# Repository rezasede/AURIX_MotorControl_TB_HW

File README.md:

# GaN FET PMSM Motor Control Test Bench — PCB Hardware

A two-board, 3-phase **GaN-based inverter** for driving a **PMSM / BLDC motor** with Field-Oriented Control (FOC).
The design takes inspiration from Infineon's CoolGaN™ motor-drive evaluation boards (EVAL-MTR-48V150A-GaN), whose user manuals are kept in this folder for reference.

| Board | KiCad project | Purpose |
|---|---|---|
| **Power board** | [`KicadPower/MotorDrive_Power`](KicadPower/MotorDrive_Power.kicad_pro) | 3-phase GaN half-bridges, gate drivers, current / voltage / temperature sensing, DC-link capacitors |
| **Control board** | [`KicadControlAURIX/MotorDrive_Control_AURIX`](KicadControlAURIX/MotorDrive_Control_AURIX.kicad_pro) | Carrier for the Infineon **AURIX™ TC4D7 Lite kit (A3G)**, logic supply, user I/O, 40-pin link to the power board |

---

## 1. System overview

```mermaid
flowchart LR
    DC[("DC supply<br/>≤ 48 V nominal")] -->|+Vin| PWR

    subgraph CTRL["🧠 Control board — AURIX carrier"]
        direction TB
        JACK["Power jack"] --> BUCK["MIC28515<br/>buck"] --> LDO1["LDK220C<br/>LDO"]
        MCU["AURIX TC4D7<br/>Lite kit"]
        UI["LEDs · Button · POT<br/>UART · 5-pin connectors"]
        UI --- MCU
        LDO1 --> MCU
    end

    subgraph PWR["⚡ Power board — 6-layer"]
        direction TB
        GD["Gate drivers<br/>6× 1EDN7116G"]
        PS["GaN power stage<br/>24× IGB110S101"]
        SNS["Sensing<br/>3× TLE4972 + Vph"]
        TMP["Temp sensors<br/>3× TMP1075"]
        CAP["Bulk caps<br/>DC link"]
        GD --> PS --> SNS
        CAP --- PS
    end

    MCU <==>|"40-pin header<br/>(P_HS/P_LS, IP, VP, OCD, TEMP)"| PWR
    SNS ==>|"Phase R / S / T"| M(("PMSM<br/>motor"))
```

---

## 2. Power board

### 2.1 Schematic hierarchy

The root sheet `MotorDrive_Power.kicad_sch` reuses one sheet per function and instantiates it **three times — once per phase**.

```mermaid
flowchart TD
    ROOT["MotorDrive_Power.kicad_sch<br/>(root: input connectors, TVS SMBJ48A, LED)"]
    ROOT --> CON["Connector<br/>Header 20×2 · LDK220C-R"]
    ROOT --> BULK["Bulk_Caps<br/>6× 100 µF 50 V · 2× 47 µF 50 V"]

    ROOT --> GD1["GateDrive"] & GD2["GateDrive_1"] & GD3["GateDrive_2"]
    ROOT --> PS1["PowerStage"] & PS2["PowerStage_1"] & PS3["PowerStage_2"]
    ROOT --> SN1["Sensing"] & SN2["Sensing_1"] & SN3["Sensing_2"]
    ROOT --> TS1["TempSensor"] & TS2["TempSensor_1"] & TS3["TempSensor_2"]

    classDef ph fill:#e8f1ff,stroke:#3b6fd8,color:#000
    classDef shared fill:#fff4e0,stroke:#d08a1a,color:#000
    class GD1,GD2,GD3,PS1,PS2,PS3,SN1,SN2,SN3,TS1,TS2,TS3 ph
    class CON,BULK shared
```

### 2.2 One phase leg

Each phase is a half-bridge with **4 paralleled GaN HEMTs on the high side and 4 on the low side** (8 × IGB110S101 per phase, 24 in total). Each switch group has its own single-channel gate driver.

```mermaid
flowchart LR
    MCU_HS["HS_MCU<br/>(PWM)"] --> DRV_HS["1EDN7116G<br/>high-side driver"]
    MCU_LS["LS_MCU<br/>(PWM)"] --> DRV_LS["1EDN7116G<br/>low-side driver"]

    BOOT["SS34 bootstrap<br/>+ LDK220C LDO<br/>+ 5.6 V Zener clamp"] -.supply.-> DRV_HS
    LDO["LDK220C-R LDO<br/>from +10 V"] -.supply.-> DRV_LS

    DRV_HS -->|HS gate| HS["High side<br/>4× IGB110S101 ∥"]
    DRV_LS -->|LS gate| LS["Low side<br/>4× IGB110S101 ∥"]

    VIN(["+Vin"]) --- HS
    HS --- SW(("SW node"))
    SW --- LS
    LS --- GND(["GND"])

    SW --> CS["TLE4972-AE35S5<br/>coreless current sensor"]
    CS -->|Iph_P / Iph_N| OUT1["to MCU (diff.)"]
    CS -->|OCD| OUT2["Over-current flag"]
    SW --> VDIV["Divider"] -->|Vph| OUT3["to MCU ADC"]
    CS --> PHASE(("Phase<br/>R/S/T"))
```

> The PowerStage sheet also carries a note for the alternative part **IGB070S10S1**.

### 2.3 Power tree

```mermaid
flowchart TD
    VIN["+Vin (DC bus, ≤48 V)"] --> TVS["SMBJ48A TVS"]
    VIN --> DCL["DC-link: 6×100 µF + 2×47 µF bulk<br/>+ ceramic decoupling per phase"]
    VIN --> HB["3× GaN half-bridges"]
    P10["+10 V (from control board)"] --> LDOG["LDK220C(-R) per driver"] --> GDRV["Gate-driver supply"]
    P10 --> LDOC["LDK220C-R (Connector sheet)"] --> P33S["+3V3_SNS<br/>current sensors"]
    P33["+3V3 (from control board)"] --> TMPS["TMP1075 / logic"]
```

### 2.4 Signals on the 40-pin board-to-board header

| Signal | Count | Direction (power board) | Description |
|---|---|---|---|
| `P_HS[1..3]` | 3 | in | High-side PWM per phase |
| `P_LS[1..3]` | 3 | in | Low-side PWM per phase |
| `IP_P[1..3]`, `IP_N[1..3]` | 6 | out | Differential phase-current outputs (TLE4972) |
| `VP[1..3]` | 3 | out | Phase-voltage sense |
| `OCD` | 1 | bidir | Wired over-current detect from current sensors |
| `TEMP{…}` | bus | passive | I²C bus to the three TMP1075 sensors (A0–A2 address straps) |
| `+Vin`, `+10V`, `+3V3`, `GND` | — | power | Supply rails |

Dedicated KiCad net classes exist for `P_HS`, `P_LS`, `IP_P`, `IP_N`, `VP` (with a 100 Ω tuning profile for the current-sense pairs).

### 2.5 Key components

| Function | Part | Qty |
|---|---|---|
| GaN HEMT, 100 V | Infineon **IGB110S101** (PG-VSON-4) | 24 |
| Gate driver | Infineon **1EDN7116GXTMA1** | 6 |
| Current sensor | Infineon **TLE4972-AE35S5** (coreless, with OCD) | 3 |
| Temperature sensor | TI **TMP1075DGKR** (I²C) | 3 |
| LDO | ST **LDK220C / LDK220C-R** | 7 |
| Bootstrap diode | SS34 | 3 per phase |
| Input TVS | SMBJ48A | 1 |
| Bulk capacitors | 100 µF 50 V / 47 µF 50 V | 6 / 2 |

```mermaid
pie showData title Power board — main active devices
    "GaN FETs (IGB110S101)" : 24
    "Gate drivers (1EDN7116G)" : 6
    "LDOs (LDK220C)" : 7
    "Current sensors (TLE4972)" : 3
    "Temp sensors (TMP1075)" : 3
```

### 2.6 PCB

| Parameter | Value |
|---|---|
| Size | **91 × 71 mm** |
| Copper layers | **6** (F.Cu, In1–In4, B.Cu) |
| Board thickness | ≈ 1.56 mm |
| Footprints | 343 |
| Vias / track segments / zones | 1476 / 1064 / 35 |
| Default rules | 0.2 mm track, 0.1 mm clearance, 0.6/0.3 mm via |

```text
   ┌──────────────── 6-layer stack ────────────────┐
   │ F.Cu   ▓▓▓▓▓▓▓▓▓▓▓▓▓▓▓▓▓▓▓▓▓▓▓▓▓▓▓▓▓▓▓▓▓▓▓▓▓▓ │  GaN FETs, drivers, power copper
   │ In1.Cu ░░░░░░░░░░░░░░░░░░░░░░░░░░░░░░░░░░░░░░ │
   │ In2.Cu ░░░░░░░░░░░░░░░░░░░░░░░░░░░░░░░░░░░░░░ │  inner planes / power-loop return
   │ In3.Cu ░░░░░░░░░░░░░░░░░░░░░░░░░░░░░░░░░░░░░░ │
   │ In4.Cu ░░░░░░░░░░░░░░░░░░░░░░░░░░░░░░░░░░░░░░ │
   │ B.Cu   ▓▓▓▓▓▓▓▓▓▓▓▓▓▓▓▓▓▓▓▓▓▓▓▓▓▓▓▓▓▓▓▓▓▓▓▓▓▓ │
   └────────────────────── ≈1.56 mm ───────────────┘
```

---

## 3. Control board (AURIX carrier)

```mermaid
flowchart TD
    ROOT["MotorDrive_Control_AURIX.kicad_sch"] --> PSU["PSU sheet"]
    ROOT --> CTL["Control sheet"]

    PSU --> J["Power jack"] --> T["SMBJ10A TVS"] --> B["MIC28515T-E/PHA<br/>sync. buck + inductor<br/>220 µF / 47 µF"] --> L["LDK220C-R LDO"]

    CTL --> HDR["Header 20×2<br/>→ power board"]
    CTL --> KIT["AURIX TC4D7 Lite kit pins<br/>P00 · P03 · P15 · P16 · P20–P23 · P32 · P33<br/>AN0–AN21 · /PORST · /ESR0-1"]
    CTL --> IO["4× LED · Button · POT<br/>UART TX/RX · 2× 5-pin conn · 4-pin conn<br/>3-pin SMD jumper"]
```

| Parameter | Value |
|---|---|
| Size | **145.9 × 100 mm** |
| Copper layers | 2 |
| Board thickness | ≈ 1.69 mm |
| Footprints | 114 |
| Vias / track segments / zones | 431 / 720 / 7 |

---

## 4. Repository layout

```text
MotorControl_TB_PCB/
├── README.md
├── KicadPower/                    # Power board (KiCad)
│   ├── MotorDrive_Power.kicad_pro/.kicad_sch/.kicad_pcb/.kicad_dru
│   ├── PowerStage.kicad_sch       # 8× GaN per phase
│   ├── GateDrive.kicad_sch        # 2× 1EDN7116G per phase
│   ├── Sensing.kicad_sch          # TLE4972 + phase voltage
│   ├── TempSensor.kicad_sch       # TMP1075
│   ├── Bulk_Caps.kicad_sch
│   ├── Connector.kicad_sch        # 40-pin link to control board
│   ├── MotorDrive_Power.csv       # early BOM export
│   └── Lib/                       # 1EDN7116GXTMA1 symbol + footprint
├── KicadControlAURIX/             # Control board (KiCad)
│   ├── MotorDrive_Control_AURIX.*
│   ├── PSU.kicad_sch / Control.kicad_sch
│   └── AURIX A3G TC4D7 Lite kit user guide (PDF)
├── Tags/                          # Released packages: Power_V1.0.zip, control_V1.0.zip
└── Infineon CoolGaN eval-board user manuals (PDF)
```

---

## 5. Project timeline & current status

```mermaid
timeline
    title Development history
    2026-04-02 : Initial commit
               : Migration to KiCad and fixes
    2026-04-03 : New G-series gate driver (1EDN7116G) integrated
    2026-04-05 : Control board routed
               : V1.0 sent for manufacturing
    2026-06-22 : Reference PDFs added
    2026-10-24 : Power board rev. after V1.0 (work in progress, uncommitted)
```

```mermaid
stateDiagram-v2
    direction LR
    [*] --> Schematic
    Schematic --> Layout
    Layout --> V1_0_Fab: Apr 2026
    V1_0_Fab --> Rework: Oct 2026
    Rework --> V1_1_Review: next
    V1_1_Review --> Bring_up
    Bring_up --> FOC_tests
    note right of Rework
        Current state: power board
        being revised in KiCad
    end note
```

### Status checklist

- [x] Power-board schematic (3-phase, hierarchical)
- [x] Control-board schematic (AURIX carrier + PSU)
- [x] Both PCBs laid out
- [x] **V1.0** released to manufacturing — packages in [`Tags/`](Tags)
- [ ] **Power-board revision after V1.0 (in progress, uncommitted)**
  - Sensing: 3-pin SMD jumper + 2-pin header replaced by a `Conn_01x03` with 10 Ω / 4.7 kΩ
  - GateDrive: bootstrap diodes moved to an `SS34` library symbol (3 per phase)
  - Connector / TempSensor sheets updated, PCB re-routed, net classes added
- [ ] Commit and tag the revised power board
- [ ] Board bring-up: supplies, gate drive, sensor calibration
- [ ] FOC firmware on the AURIX and motor tests

---

## 6. Tools & references

- **KiCad** (projects migrated from Altium; most parts come from the `RezaLIB` library)
- Infineon *EVAL-MTR-48V150A-GaN* user manual
- Infineon *FOC motor-drive evaluation board based on CoolGaN™ transistors* user manual
- Infineon *KIT_A3G_TC4D7_LITE* user guide (in `KicadControlAURIX/`)

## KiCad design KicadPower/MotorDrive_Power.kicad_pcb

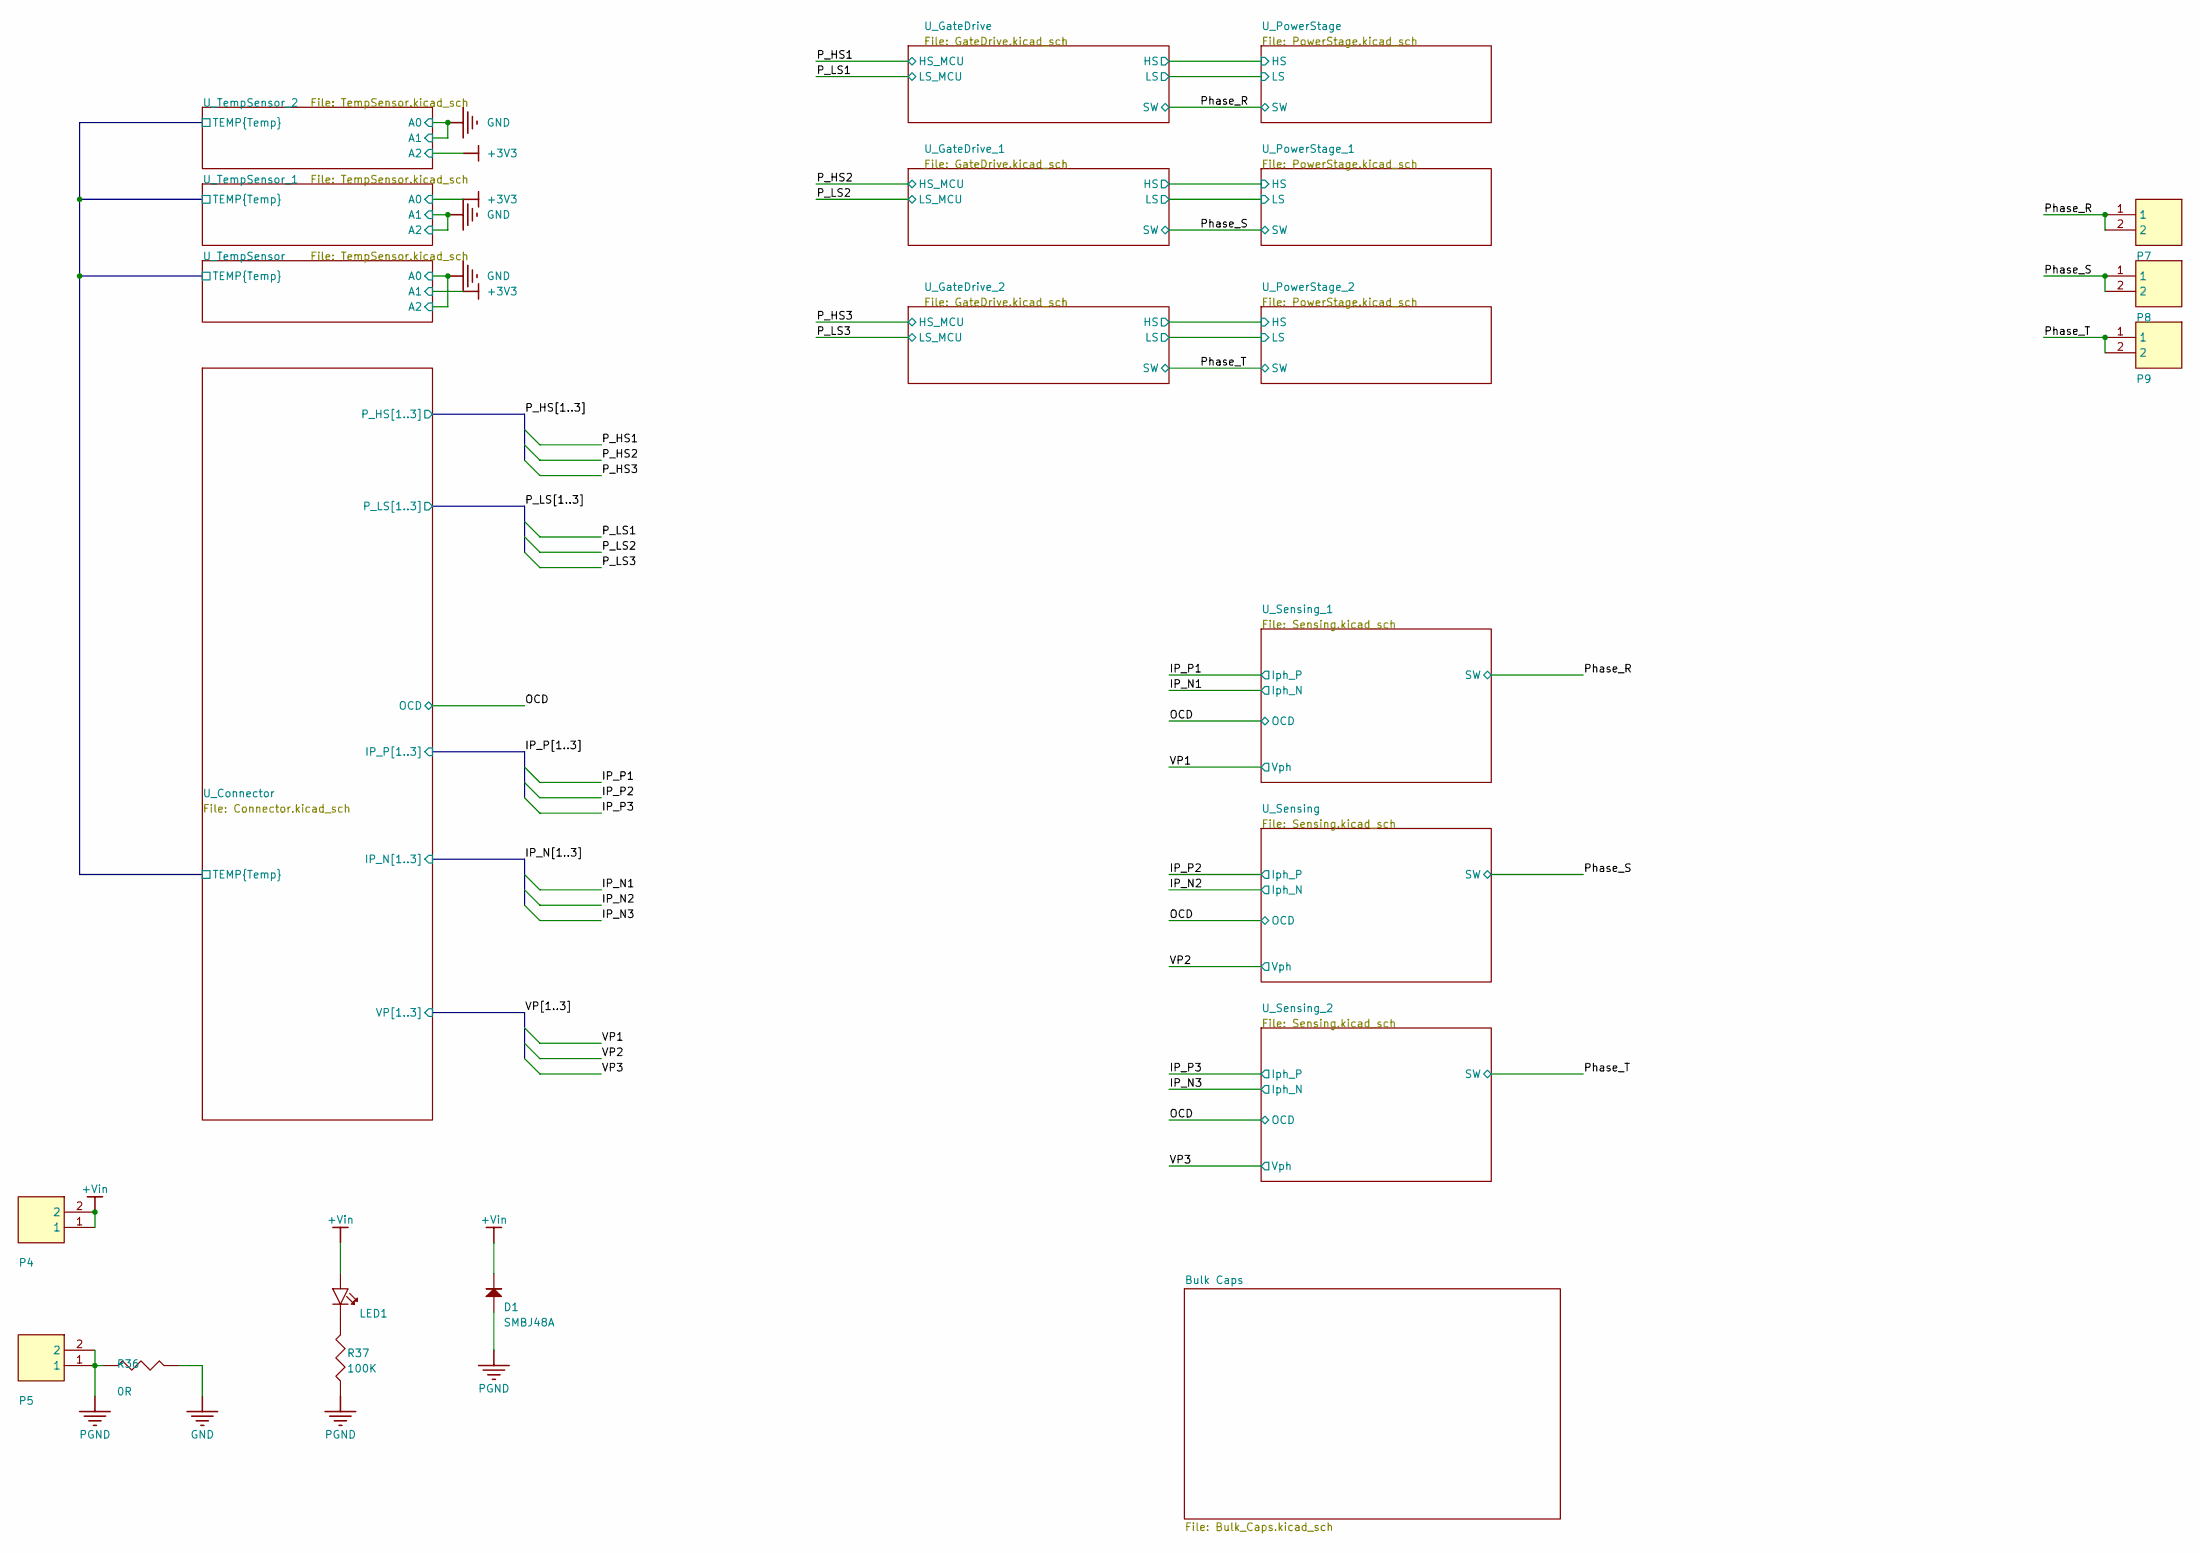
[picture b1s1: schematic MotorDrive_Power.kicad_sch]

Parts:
D1: SMBJ48A; DO-214AA
LED1: LED; LED0603
P4, P5, P7, P8, P9: Connector; Terminal Block 2pin
R36: Res SMD; RESC3225X70N
R37: Res SMD; RESC1608X55N

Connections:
+Vin: D1.K (2), LED1.1 (A), P4.1, P4.2; also elsewhere on the board
/Phase_R: P7.1, P7.2; also elsewhere on the board
/Phase_S: P8.1, P8.2; also elsewhere on the board
/Phase_T: P9.1, P9.2; also elsewhere on the board
GND: R36.2; also elsewhere on the board
unnamed: LED1.2 (K), R37.2
PGND: D1.A (1), P5.1, P5.2, R36.1, R37.1; also elsewhere on the board

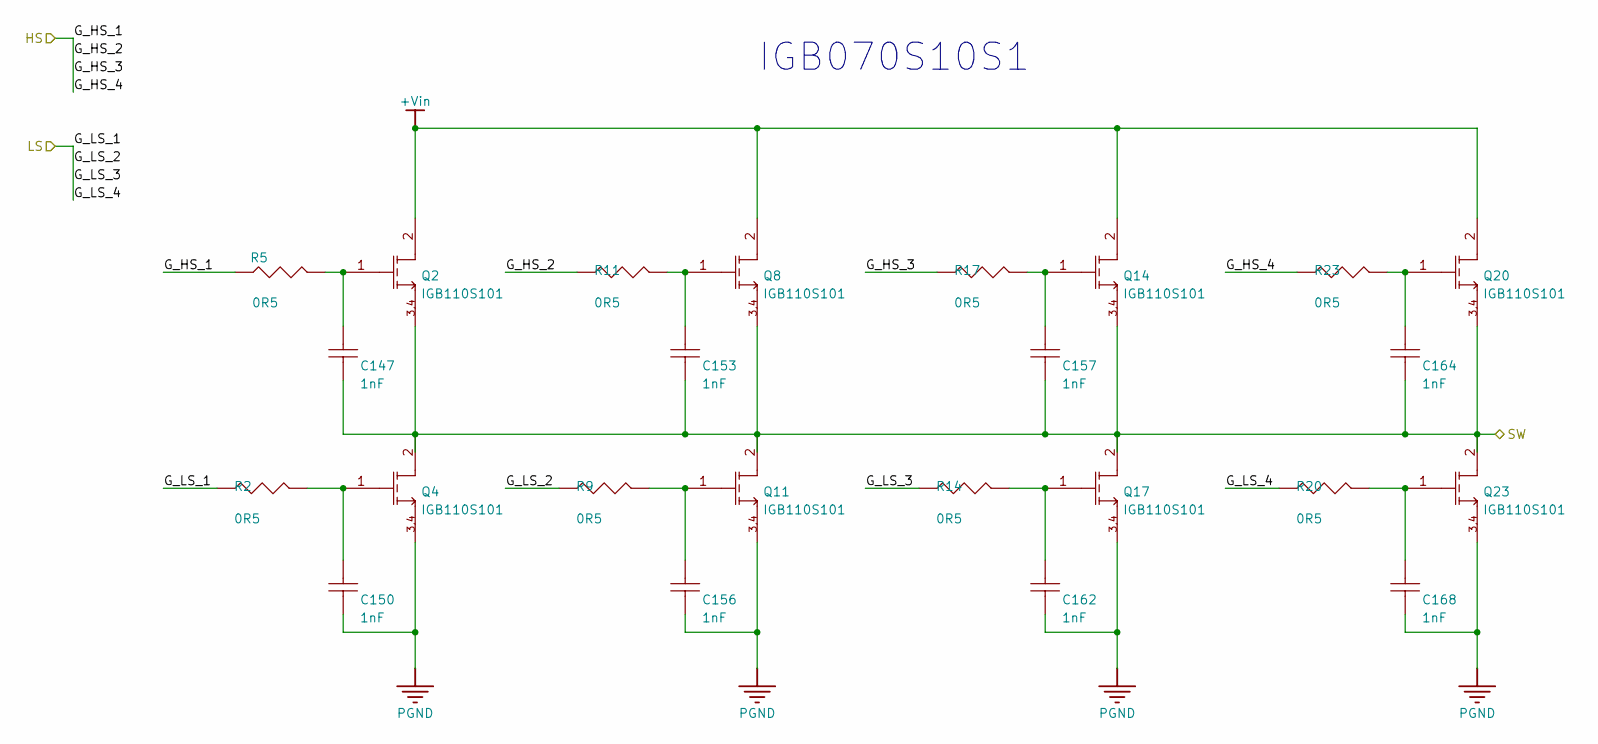
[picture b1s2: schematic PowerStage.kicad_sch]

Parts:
C147, C150, C153, C156, C157, C162, C164, C168: Cap SMD; CAPC1608X90N
Q2, Q4, Q8, Q11, Q14, Q17, Q20, Q23: IGB110S101; IFX-PG-VSON-4-3-V
R2, R5, R9, R11, R14, R17, R20, R23: Res SMD; RESC1608X55N

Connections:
+Vin: Q2.2 (D), Q8.2 (D), Q14.2 (D), Q20.2 (D); also elsewhere on the board
/Phase_R: C147.1, C153.1, C157.1, C164.1, Q2.3 (S1), Q2.4 (S2), Q4.2 (D), Q8.3 (S1), Q8.4 (S2), Q11.2 (D), Q14.3 (S1), Q14.4 (S2), Q17.2 (D), Q20.3 (S1), Q20.4 (S2), Q23.2 (D); also elsewhere on the board
/U_PowerStage/G_HS_1: R5.1, R11.1, R17.1, R23.1; also elsewhere on the board
/U_PowerStage/G_LS_1: R2.1, R9.1, R14.1, R20.1; also elsewhere on the board
unnamed: C147.2, Q2.1 (G), R5.2
unnamed: C150.2, Q4.1 (G), R2.2
unnamed: C153.2, Q8.1 (G), R11.2
unnamed: C156.2, Q11.1 (G), R9.2
unnamed: C157.2, Q14.1 (G), R17.2
unnamed: C162.2, Q17.1 (G), R14.2
unnamed: C164.2, Q20.1 (G), R23.2
unnamed: C168.2, Q23.1 (G), R20.2
PGND: C150.1, C156.1, C162.1, C168.1, Q4.3 (S1), Q4.4 (S2), Q11.3 (S1), Q11.4 (S2), Q17.3 (S1), Q17.4 (S2), Q23.3 (S1), Q23.4 (S2); also elsewhere on the board

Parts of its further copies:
C145, C146, C148, C149, C151, C152, C154, C155, C158, C159, C160, C161, C163, C165, C166, C167: Cap SMD; CAPC1608X90N
Q1, Q3, Q5, Q6, Q7, Q9, Q10, Q12, Q13, Q15, Q16, Q18, Q19, Q21, Q22, Q24: IGB110S101; IFX-PG-VSON-4-3-V
R1, R3, R4, R6, R7, R8, R10, R12, R13, R15, R16, R18, R19, R21, R22, R24: Res SMD; RESC1608X55N

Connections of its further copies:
+Vin: Q1.2 (D), Q3.2 (D), Q7.2 (D), Q9.2 (D), Q13.2 (D), Q15.2 (D), Q19.2 (D), Q21.2 (D); also elsewhere on the board
/Phase_S: C145.1, C152.1, C159.1, C163.1, Q1.3 (S1), Q1.4 (S2), Q5.2 (D), Q7.3 (S1), Q7.4 (S2), Q10.2 (D), Q13.3 (S1), Q13.4 (S2), Q18.2 (D), Q21.3 (S1), Q21.4 (S2), Q24.2 (D); also elsewhere on the board
/Phase_T: C146.1, C151.1, C158.1, C165.1, Q3.3 (S1), Q3.4 (S2), Q6.2 (D), Q9.3 (S1), Q9.4 (S2), Q12.2 (D), Q15.3 (S1), Q15.4 (S2), Q16.2 (D), Q19.3 (S1), Q19.4 (S2), Q22.2 (D); also elsewhere on the board
/U_PowerStage_1/G_HS_1: R4.1, R10.1, R18.1, R22.1; also elsewhere on the board
/U_PowerStage_1/G_LS_1: R1.1, R7.1, R15.1, R19.1; also elsewhere on the board
/U_PowerStage_2/G_HS_1: R6.1, R12.1, R16.1, R24.1; also elsewhere on the board
/U_PowerStage_2/G_LS_1: R3.1, R8.1, R13.1, R21.1; also elsewhere on the board
unnamed: C145.2, Q1.1 (G), R4.2
unnamed: C146.2, Q3.1 (G), R6.2
unnamed: C149.2, Q5.1 (G), R1.2
unnamed: C148.2, Q6.1 (G), R3.2
unnamed: C152.2, Q7.1 (G), R10.2
unnamed: C151.2, Q9.1 (G), R12.2
unnamed: C155.2, Q10.1 (G), R7.2
unnamed: C154.2, Q12.1 (G), R8.2
unnamed: C159.2, Q13.1 (G), R18.2
unnamed: C158.2, Q15.1 (G), R16.2
unnamed: C161.2, Q16.1 (G), R13.2
unnamed: C160.2, Q18.1 (G), R15.2
unnamed: C165.2, Q19.1 (G), R24.2
unnamed: C163.2, Q21.1 (G), R22.2
unnamed: C167.2, Q22.1 (G), R21.2
unnamed: C166.2, Q24.1 (G), R19.2
PGND: C148.1, C149.1, C154.1, C155.1, C160.1, C161.1, C166.1, C167.1, Q5.3 (S1), Q5.4 (S2), Q6.3 (S1), Q6.4 (S2), Q10.3 (S1), Q10.4 (S2), Q12.3 (S1), Q12.4 (S2), Q16.3 (S1), Q16.4 (S2), Q18.3 (S1), Q18.4 (S2), Q22.3 (S1), Q22.4 (S2), Q24.3 (S1), Q24.4 (S2); also elsewhere on the board

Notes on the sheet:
IGB070S10S1

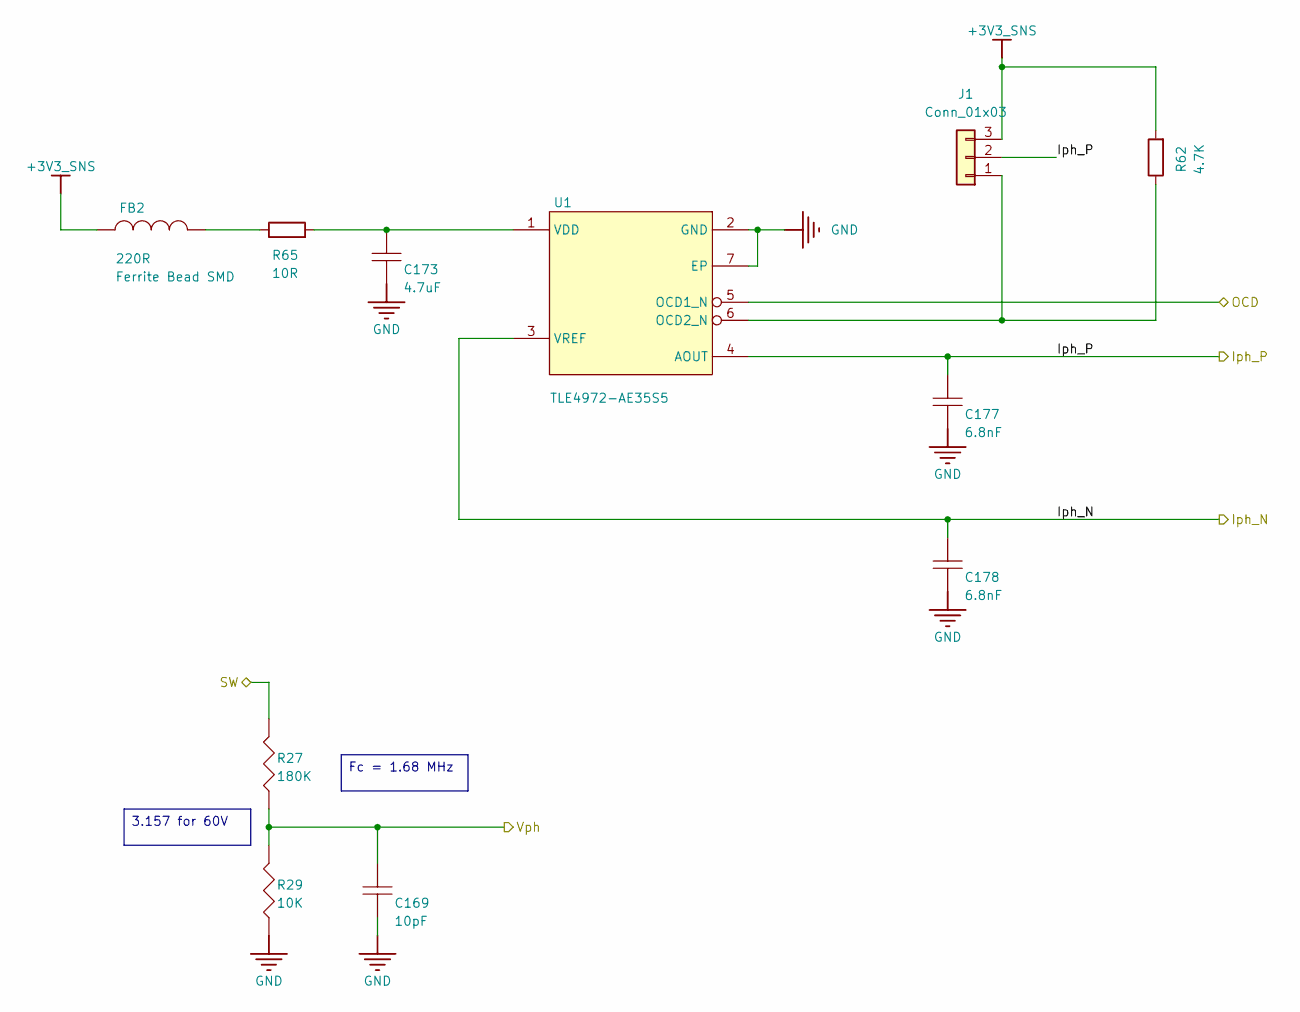
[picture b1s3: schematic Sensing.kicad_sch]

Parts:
C169, C177, C178: Cap SMD; CAPC1608X90N
C173: Cap SMD; CAPC2012X135N
FB2: Ferrite Bead SMD; RESC2012X70N
J1: Conn_01x03; PinHeader_1x03_P2.54mm_Vertical
R27, R29: Res SMD; RESC1608X55N
R62: 4.7K; R_0603_1608Metric_Pad0.98x0.95mm_HandSolder
R65: 10R; R_0603_1608Metric_Pad0.98x0.95mm_HandSolder
U1: TLE4972-AE35S5; IFX-PG-VSON-6-V

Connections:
+3V3_SNS: FB2.1, J1.3, R62.2; also elsewhere on the board
/IP_N1: C178.2, U1.3 (VREF); also elsewhere on the board
/IP_P1: C177.2, J1.2, U1.4 (AOUT); also elsewhere on the board
/OCD: U1.5 (OCD1_N); also elsewhere on the board
/Phase_R: R27.2; also elsewhere on the board
/VP1: C169.2, R27.1, R29.2; also elsewhere on the board
GND: C169.1, C173.1, C177.1, C178.1, R29.1, U1.2 (GND), U1.7 (EP); also elsewhere on the board
unnamed: FB2.2, R65.1
unnamed: J1.1, R62.1, U1.6 (OCD2_N)
unnamed: C173.2, R65.2, U1.1 (VDD)

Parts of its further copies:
C170, C171, C175, C176, C179, C180: Cap SMD; CAPC1608X90N
C172, C174: Cap SMD; CAPC2012X135N
FB1, FB3: Ferrite Bead SMD; RESC2012X70N
J2, J3: Conn_01x03; PinHeader_1x03_P2.54mm_Vertical
R25, R26, R28, R30: Res SMD; RESC1608X55N
R63, R64: 4.7K; R_0603_1608Metric_Pad0.98x0.95mm_HandSolder
R66, R67: 10R; R_0603_1608Metric_Pad0.98x0.95mm_HandSolder
U2, U3: TLE4972-AE35S5; IFX-PG-VSON-6-V

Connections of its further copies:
+3V3_SNS: FB1.1, FB3.1, J2.3, J3.3, R63.2, R64.2; also elsewhere on the board
/IP_N2: C179.2, U2.3 (VREF); also elsewhere on the board
/IP_N3: C180.2, U3.3 (VREF); also elsewhere on the board
/IP_P2: C176.2, J2.2, U2.4 (AOUT); also elsewhere on the board
/IP_P3: C175.2, J3.2, U3.4 (AOUT); also elsewhere on the board
/OCD: U2.5 (OCD1_N), U3.5 (OCD1_N); also elsewhere on the board
/Phase_S: R25.2; also elsewhere on the board
/Phase_T: R26.2; also elsewhere on the board
/VP2: C170.2, R25.1, R30.2; also elsewhere on the board
/VP3: C171.2, R26.1, R28.2; also elsewhere on the board
GND: C170.1, C171.1, C172.1, C174.1, C175.1, C176.1, C179.1, C180.1, R28.1, R30.1, U2.2 (GND), U2.7 (EP), U3.2 (GND), U3.7 (EP); also elsewhere on the board
unnamed: FB1.2, R67.1
unnamed: FB3.2, R66.1
unnamed: J2.1, R63.1, U2.6 (OCD2_N)
unnamed: J3.1, R64.1, U3.6 (OCD2_N)
unnamed: C174.2, R66.2, U2.1 (VDD)
unnamed: C172.2, R67.2, U3.1 (VDD)

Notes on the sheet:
Fc = 1.68 MHz
3.157 for 60V

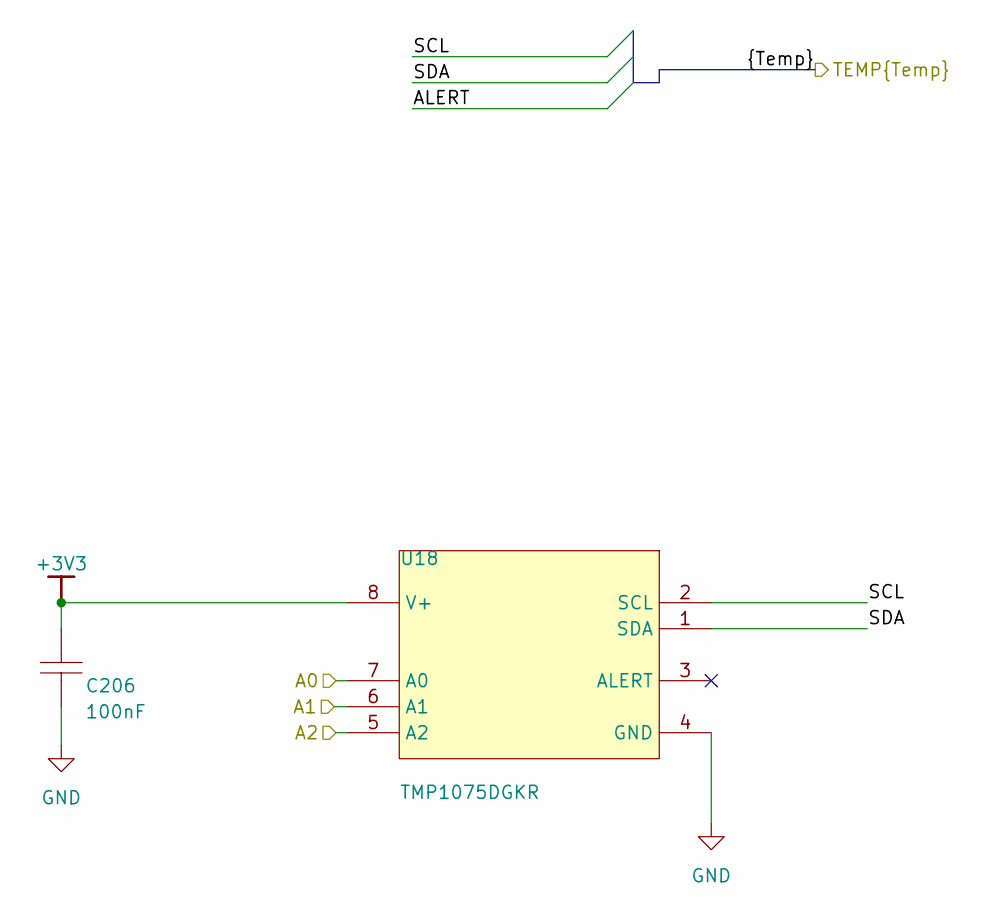
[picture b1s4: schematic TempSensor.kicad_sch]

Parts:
C206: Cap SMD; CAPC1608X90N
U18: TMP1075DGKR; DGK0008A_N; MANUFACTURER_PART_NUMBER TMP1075DGKR

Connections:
+3V3: C206.2, U18.5 (A2), U18.8 (V+); also elsewhere on the board
/U_Connector/SCL: U18.2 (SCL); also elsewhere on the board
/U_Connector/SDA: U18.1 (SDA); also elsewhere on the board
GND: C206.1, U18.4 (GND), U18.6 (A1), U18.7 (A0); also elsewhere on the board

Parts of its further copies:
C207, C208: Cap SMD; CAPC1608X90N
U17, U19: TMP1075DGKR; DGK0008A_N; MANUFACTURER_PART_NUMBER TMP1075DGKR

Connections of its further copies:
+3V3: C207.2, C208.2, U17.7 (A0), U17.8 (V+), U19.6 (A1), U19.8 (V+); also elsewhere on the board
/U_Connector/SCL: U17.2 (SCL), U19.2 (SCL); also elsewhere on the board
/U_Connector/SDA: U17.1 (SDA), U19.1 (SDA); also elsewhere on the board
GND: C207.1, C208.1, U17.4 (GND), U17.5 (A2), U17.6 (A1), U19.4 (GND), U19.5 (A2), U19.7 (A0); also elsewhere on the board

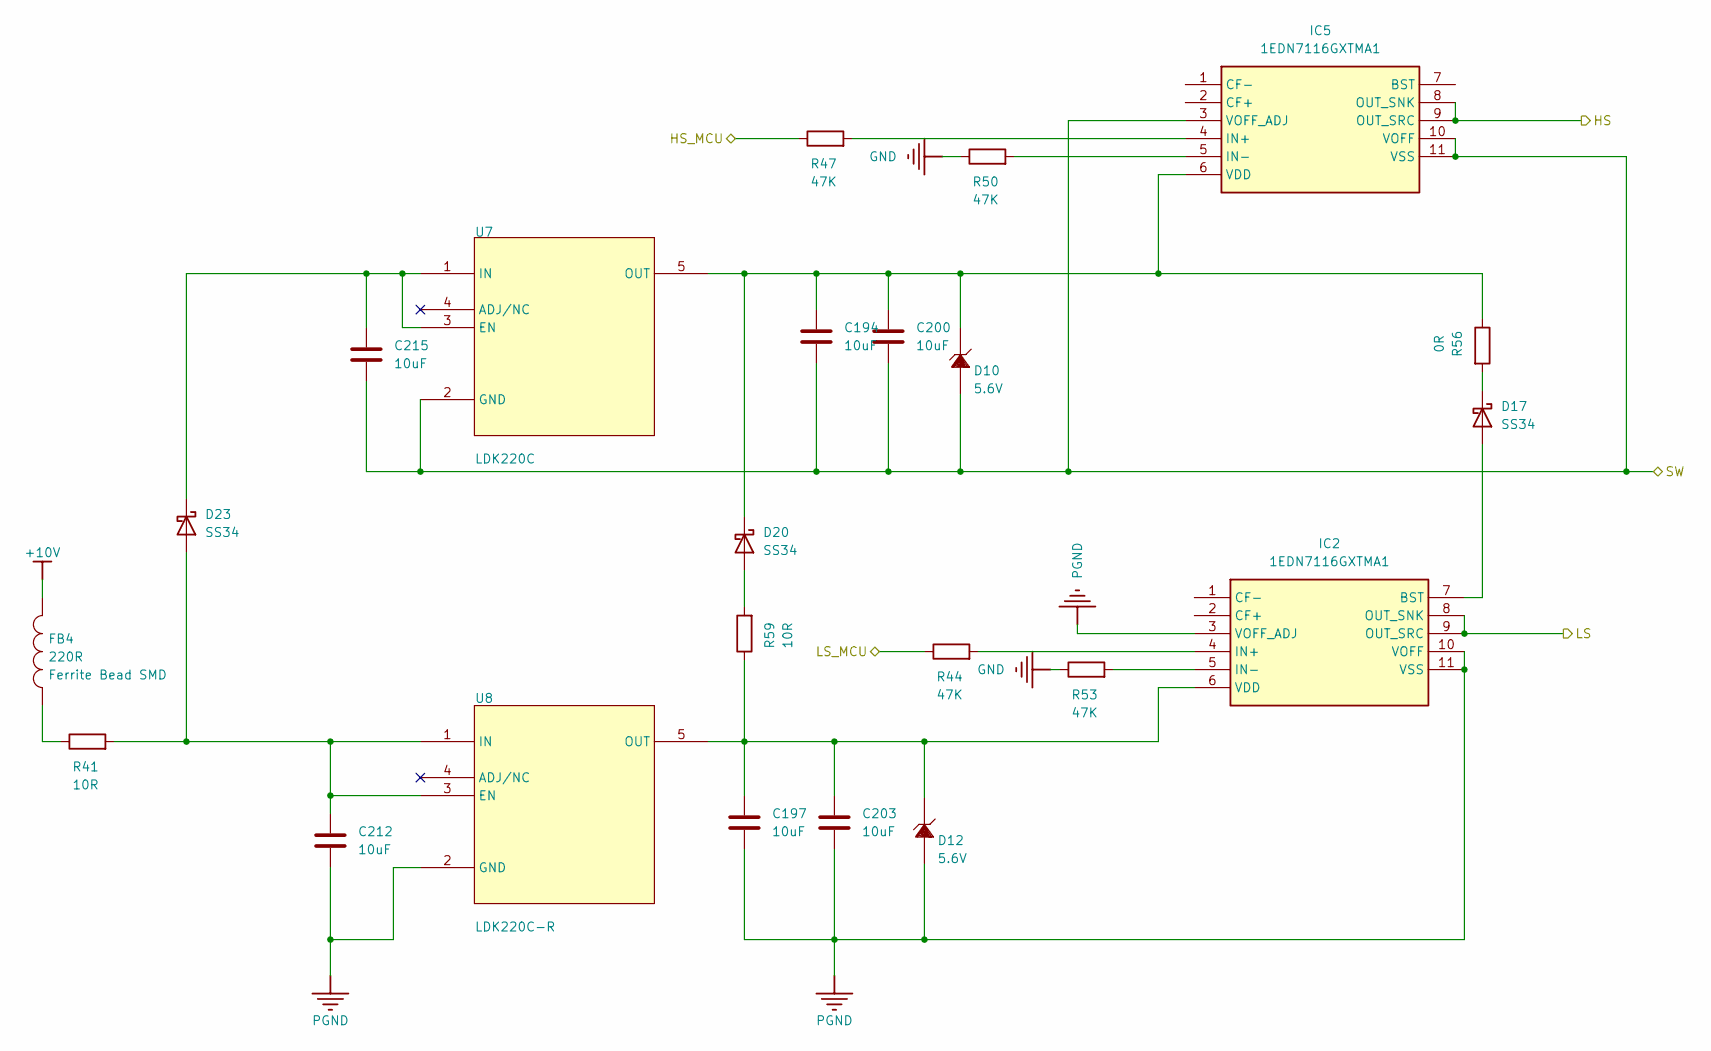
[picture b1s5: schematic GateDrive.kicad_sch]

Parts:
C194, C197, C200, C203, C212, C215: 10uF; C_0603_1608Metric
D10, D12: 5.6V; DIOMELF3615N
D17, D20, D23: SS34; D_SMA
FB4: Ferrite Bead SMD; RESC2012X70N
IC2, IC5: 1EDN7116GXTMA1; Manufacturer_Part_Number 1EDN7116GXTMA1; Mouser Part Number 726-1EDN7116GXTMA1
R41, R59: 10R; R_0603_1608Metric_Pad0.98x0.95mm_HandSolder
R44, R47, R50, R53: 47K; R_0603_1608Metric_Pad0.98x0.95mm_HandSolder
R56: 0R; R_0603_1608Metric_Pad0.98x0.95mm_HandSolder
U7: LDK220C; SOT_220M-R_STM; MANUFACTURER_PART_NUMBER LDK220C-R
U8: LDK220C-R; SOT_220M-R_STM; MANUFACTURER_PART_NUMBER LDK220C-R

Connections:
+10V: FB4.2; also elsewhere on the board
/P_HS1: R47.1; also elsewhere on the board
/P_LS1: R44.1; also elsewhere on the board
/Phase_R: C194.2, C200.2, C215.2, D10.2, IC5.3 (VOFF_ADJ), IC5.10 (VOFF), IC5.11 (VSS), U7.2 (GND); also elsewhere on the board
/U_PowerStage/G_HS_1: IC5.8 (OUT_SNK), IC5.9 (OUT_SRC); also elsewhere on the board
/U_PowerStage/G_LS_1: IC2.8 (OUT_SNK), IC2.9 (OUT_SRC); also elsewhere on the board
GND: R50.1, R53.1; also elsewhere on the board
unnamed: D17.2 (A), IC2.7 (BST)
unnamed: D17.1 (K), R56.2
unnamed: D20.2 (A), R59.2
unnamed: C194.1, C200.1, D10.1, D20.1 (K), IC5.6 (VDD), R56.1, U7.5 (OUT)
unnamed: C212.1, D23.2 (A), R41.2, U8.1 (IN), U8.3 (EN)
unnamed: C215.1, D23.1 (K), U7.1 (IN), U7.3 (EN)
unnamed: FB4.1, R41.1
unnamed: IC2.4 (IN+), R44.2
unnamed: IC2.5 (IN-), R53.2
unnamed: C197.1, C203.1, D12.1, IC2.6 (VDD), R59.1, U8.5 (OUT)
unnamed: IC5.4 (IN+), R47.2
unnamed: IC5.5 (IN-), R50.2
PGND: C197.2, C203.2, C212.2, D12.2, IC2.3 (VOFF_ADJ), IC2.10 (VOFF), IC2.11 (VSS), U8.2 (GND); also elsewhere on the board

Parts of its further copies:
C195, C196, C198, C199, C201, C202, C204, C205, C213, C214, C216, C217: 10uF; C_0603_1608Metric
D8, D9, D11, D13: 5.6V; DIOMELF3615N
D18, D19, D21, D22, D24, D25: SS34; D_SMA
FB5, FB6: Ferrite Bead SMD; RESC2012X70N
IC3, IC4, IC6, IC7: 1EDN7116GXTMA1; Manufacturer_Part_Number 1EDN7116GXTMA1; Mouser Part Number 726-1EDN7116GXTMA1
R42, R43, R60, R61: 10R; R_0603_1608Metric_Pad0.98x0.95mm_HandSolder
R45, R46, R48, R49, R51, R52, R54, R55: 47K; R_0603_1608Metric_Pad0.98x0.95mm_HandSolder
R57, R58: 0R; R_0603_1608Metric_Pad0.98x0.95mm_HandSolder
U5, U6: LDK220C; SOT_220M-R_STM; MANUFACTURER_PART_NUMBER LDK220C-R
U9, U10: LDK220C-R; SOT_220M-R_STM; MANUFACTURER_PART_NUMBER LDK220C-R

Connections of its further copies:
+10V: FB5.2, FB6.2; also elsewhere on the board
/P_HS2: R48.1; also elsewhere on the board
/P_HS3: R49.1; also elsewhere on the board
/P_LS2: R45.1; also elsewhere on the board
/P_LS3: R46.1; also elsewhere on the board
/Phase_S: C195.2, C201.2, C216.2, D9.2, IC6.3 (VOFF_ADJ), IC6.10 (VOFF), IC6.11 (VSS), U6.2 (GND); also elsewhere on the board
/Phase_T: C196.2, C202.2, C217.2, D8.2, IC7.3 (VOFF_ADJ), IC7.10 (VOFF), IC7.11 (VSS), U5.2 (GND); also elsewhere on the board
/U_PowerStage_1/G_HS_1: IC6.8 (OUT_SNK), IC6.9 (OUT_SRC); also elsewhere on the board
/U_PowerStage_1/G_LS_1: IC3.8 (OUT_SNK), IC3.9 (OUT_SRC); also elsewhere on the board
/U_PowerStage_2/G_HS_1: IC7.8 (OUT_SNK), IC7.9 (OUT_SRC); also elsewhere on the board
/U_PowerStage_2/G_LS_1: IC4.8 (OUT_SNK), IC4.9 (OUT_SRC); also elsewhere on the board
GND: R51.1, R52.1, R54.1, R55.1; also elsewhere on the board
unnamed: D18.2 (A), IC3.7 (BST)
unnamed: D18.1 (K), R57.2
unnamed: D19.2 (A), IC4.7 (BST)
unnamed: D19.1 (K), R58.2
unnamed: D21.2 (A), R60.2
unnamed: C195.1, C201.1, D9.1, D21.1 (K), IC6.6 (VDD), R57.1, U6.5 (OUT)
unnamed: D22.2 (A), R61.2
unnamed: C196.1, C202.1, D8.1, D22.1 (K), IC7.6 (VDD), R58.1, U5.5 (OUT)
unnamed: C213.1, D24.2 (A), R42.2, U10.1 (IN), U10.3 (EN)
unnamed: C216.1, D24.1 (K), U6.1 (IN), U6.3 (EN)
unnamed: C214.1, D25.2 (A), R43.2, U9.1 (IN), U9.3 (EN)
unnamed: C217.1, D25.1 (K), U5.1 (IN), U5.3 (EN)
unnamed: FB5.1, R43.1
unnamed: FB6.1, R42.1
unnamed: IC3.4 (IN+), R45.2
unnamed: IC3.5 (IN-), R54.2
unnamed: C198.1, C204.1, D13.1, IC3.6 (VDD), R60.1, U10.5 (OUT)
unnamed: IC4.4 (IN+), R46.2
unnamed: IC4.5 (IN-), R55.2
unnamed: C199.1, C205.1, D11.1, IC4.6 (VDD), R61.1, U9.5 (OUT)
unnamed: IC6.4 (IN+), R48.2
unnamed: IC6.5 (IN-), R51.2
unnamed: IC7.4 (IN+), R49.2
unnamed: IC7.5 (IN-), R52.2
PGND: C198.2, C199.2, C204.2, C205.2, C213.2, C214.2, D11.2, D13.2, IC3.3 (VOFF_ADJ), IC3.10 (VOFF), IC3.11 (VSS), IC4.3 (VOFF_ADJ), IC4.10 (VOFF), IC4.11 (VSS), U9.2 (GND), U10.2 (GND); also elsewhere on the board

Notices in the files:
parts and their libraries:
COPYRIGHT: Copyright (C) 2026 Ultra Librarian. All rights reserved.
COPYRIGHT: Copyright (C) 2025 Ultra Librarian. All rights reserved.
